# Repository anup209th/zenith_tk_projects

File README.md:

# zenith_tk_projects
As an intern at Zenith Tek, I created developer guides for modules like LoRa SX1278 and ADXL345, designed schematics and flash circuits for ESP32, and assisted with hardware bring-up, including sensor interfacing, PCB debugging, and firmware flashing.

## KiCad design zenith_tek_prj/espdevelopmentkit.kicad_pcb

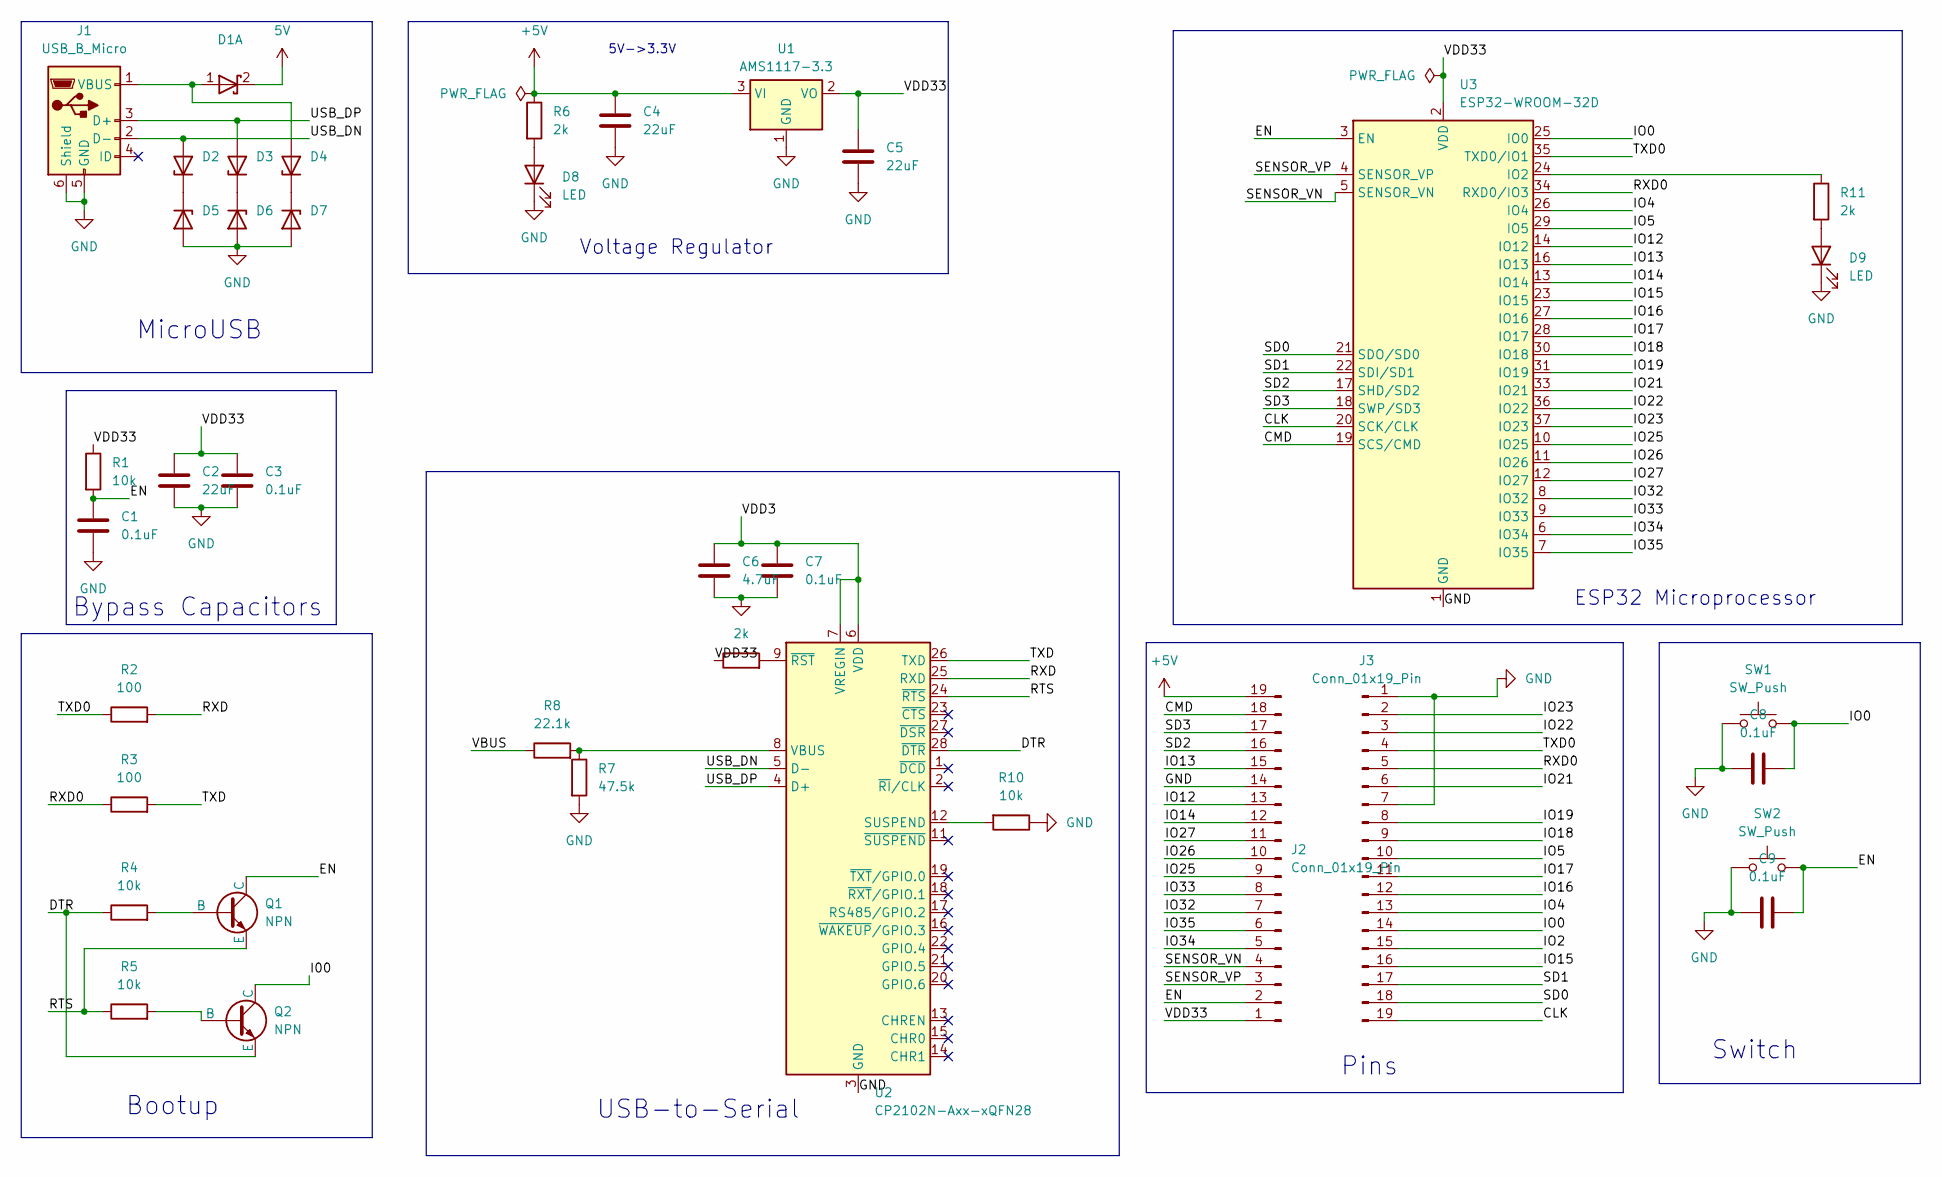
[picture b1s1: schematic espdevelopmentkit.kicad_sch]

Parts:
C1, C3, C7, C8, C9: 0.1uF; C_1206_3216Metric_Pad1.33x1.80mm_HandSolder
C2, C4, C5: 22uF; C_2220_5750Metric_Pad1.97x5.40mm_HandSolder
C6: 4.7uF; C_1210_3225Metric_Pad1.33x2.70mm_HandSolder
D1: D_Schottky_Dual_CommonAnode_AKK_Split; SOT-23
D2, D3, D4, D5, D6, D7: 1N53xxB; D_0603_1608Metric_Pad1.05x0.95mm_HandSolder
D8, D9: LED; LED_2512_6332Metric_Pad1.52x3.35mm_HandSolder
J1: USB_B_Micro; USB_Micro-B_Molex_47346-0001
J2: Conn_01x19_Pin; PinHeader_1x17_P1.00mm_Vertical
J3: Conn_01x19_Pin; PinHeader_1x19_P1.00mm_Vertical
Q1, Q2: NPN; SOT-23W
R1, R4, R5, R10: 10k; R_0805_2012Metric_Pad1.20x1.40mm_HandSolder
R2, R3: 100; R_0201_0603Metric_Pad0.64x0.40mm_HandSolder
R6, R9, R11: 2k; R_0612_1632Metric_Pad1.18x3.40mm_HandSolder
R7: 47.5k; R_1206_3216Metric_Pad1.30x1.75mm_HandSolder
R8: 22.1k; R_0815_2038Metric_Pad1.20x4.05mm_HandSolder
SW1, SW2: SW_Push; SW_PUSH_6mm_H4.3mm
U1: AMS1117-3.3; SOT-223-3_TabPin2
U2: CP2102N-Axx-xQFN28; QFN-28-1EP_5x5mm_P0.5mm_EP3.35x3.35mm
U3: ESP32-WROOM-32D

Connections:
5V: D1.2 (K)
+5V: C4.1, J2.19, R6.1, U1.3 (VI)
/CLK: J3.19, U3.20 (SCK/CLK)
/CMD: J2.18, U3.19 (SCS/CMD)
/DTR: Q2.3 (E), R4.1, U2.28 (~DTR)
/EN: C1.1, C9.2, J2.2, Q1.1 (C), R1.2, SW2.2, U3.3 (EN)
/I00: Q2.1 (C)
/IO0: C8.2, J3.14, SW1.2, U3.25 (IO0)
/IO2: J3.15
/IO4: J3.13, U3.26 (IO4)
/IO5: J3.10, U3.29 (IO5)
/IO12: J2.13, U3.14 (IO12)
/IO13: J2.15, U3.16 (IO13)
/IO14: J2.12, U3.13 (IO14)
/IO15: J3.16, U3.23 (IO15)
/IO16: J3.12, U3.27 (IO16)
/IO17: J3.11, U3.28 (IO17)
/IO18: J3.9, U3.30 (IO18)
/IO19: J3.8, U3.31 (IO19)
/IO21: J3.6, U3.33 (IO21)
/IO22: J3.3, U3.36 (IO22)
/IO23: J3.2, U3.37 (IO23)
/IO25: J2.9, U3.10 (IO25)
/IO26: J2.10, U3.11 (IO26)
/IO27: J2.11, U3.12 (IO27)
/IO32: J2.7, U3.8 (IO32)
/IO33: J2.8, U3.9 (IO33)
/IO34: J2.5, U3.6 (IO34)
/IO35: J2.6, U3.7 (IO35)
/RTS: Q1.3 (E), R5.1, U2.24 (~RTS)
/RXD: R2.2, U2.25 (RXD)
/RXD0: J3.5, R3.1, U3.34 (RXD0/IO3)
/SD0: J3.18, U3.21 (SDO/SD0)
/SD1: J3.17, U3.22 (SDI/SD1)
/SD2: J2.16, U3.17 (SHD/SD2)
/SD3: J2.17, U3.18 (SWP/SD3)
/SENSOR_VN: J2.4, U3.5 (SENSOR_VN)
/SENSOR_VP: J2.3, U3.4 (SENSOR_VP)
/TXD: R3.2, U2.26 (TXD)
/TXD0: J3.4, R2.1, U3.35 (TXD0/IO1)
/USB_DN: D2.2 (A), J1.2 (D-), U2.5 (D-)
/USB_DP: D3.2 (A), J1.3 (D+), U2.4 (D+)
/VBUS: R8.1
/VDD3: C6.1, C7.1, U2.6 (VDD), U2.7 (VREGIN)
/VDD33: C2.1, C3.1, C5.1, J2.1, R1.1, R9.1, U1.2 (VO), U3.2 (VDD)
GND: C1.2, C2.2, C3.2, C4.2, C5.2, C6.2, C7.2, C8.1, C9.1, D5.2 (A), D6.2 (A), D7.2 (A), D8.1 (K), D9.1 (K), J1.5 (GND), J1.6 (Shield), J2.14, J3.1, J3.7, R7.2, R10.1, SW1.1, SW2.1, U1.1 (GND), U2.3 (GND), U2.29 (GND), U3.1 (GND), U3.15 (GND), U3.38 (GND), U3.39 (GND)
unnamed: D1.1 (A), D4.2 (A), J1.1 (VBUS)
unnamed: D2.1 (K), D5.1 (K)
unnamed: D3.1 (K), D6.1 (K)
unnamed: D4.1 (K), D7.1 (K)
unnamed: D8.2 (A), R6.2
unnamed: D9.2 (A), R11.2
unnamed: Q1.2 (B), R4.2
unnamed: Q2.2 (B), R5.2
unnamed: R10.2, U2.12 (SUSPEND)
unnamed: R7.1, R8.2, U2.8 (VBUS)
unnamed: R9.2, U2.9 (~RST)
unnamed: R11.1, U3.24 (IO2)

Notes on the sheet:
Pins
ESP32 Microprocessor
Voltage Regulator
MicroUSB
Bypass Capacitors
USB-to-Serial
5V->3.3V
Bootup
Switch

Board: 2 copper layers, 39 parts (0 on the bottom side), 53 nets, no tracks yet.
